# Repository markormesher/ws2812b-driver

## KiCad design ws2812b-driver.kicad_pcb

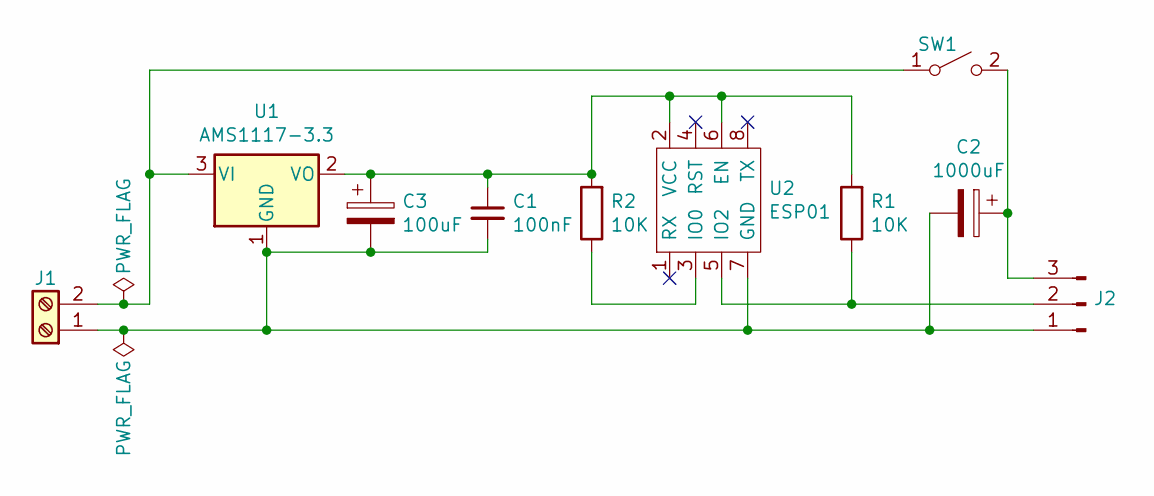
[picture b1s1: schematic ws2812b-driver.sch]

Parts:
C1: 100nF; C_Disc_D5.0mm_W2.5mm_P2.50mm
C2: 1000uF; C_Radial_D10.0mm_H20.0mm_P5.00mm
C3: 100uF; C_Radial_D6.3mm_H11.0mm_P2.50mm
J1: Screw_Terminal_01x02; TerminalBlock_bornier-2_P5.08mm
J2: Conn_01x03_Male; PinHeader_1x03_P2.54mm_Horizontal
R1, R2: 10K; R_Axial_DIN0207_L6.3mm_D2.5mm_P7.62mm_Horizontal
SW1: SW_SPST; PinHeader_1x02_P2.54mm_Vertical
U1: AMS1117-3.3; AMS1117
U2: ESP01; PinSocket_2x04_P2.54mm_Vertical

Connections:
unnamed: C1.1, C3.1, R1.2, R2.2, U1.2 (VO), U2.2 (VCC), U2.6 (EN)
unnamed: C1.2, C2.2, C3.2, J1.1, J2.1, U1.1 (GND), U2.7 (GND)
unnamed: C2.1, J2.3, SW1.2 (B)
unnamed: J1.2, SW1.1 (A), U1.3 (VI)
unnamed: J2.2, R1.1, U2.5 (IO2)
unnamed: R2.1, U2.3 (IO0)

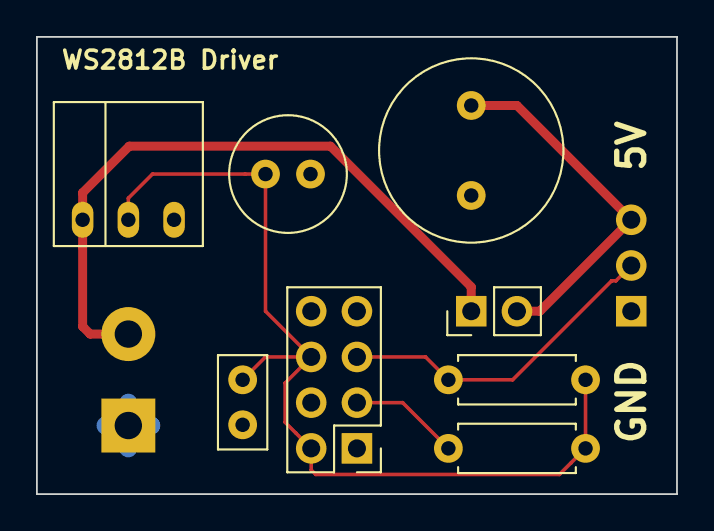
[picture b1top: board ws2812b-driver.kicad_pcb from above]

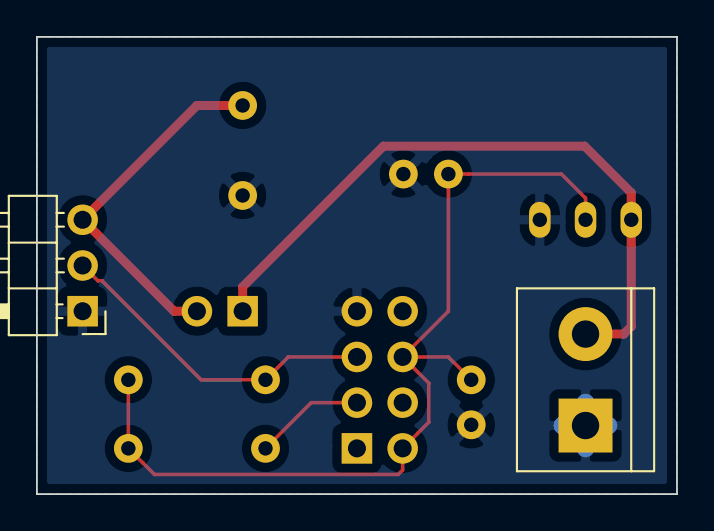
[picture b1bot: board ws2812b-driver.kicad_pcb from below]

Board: 2 copper layers, 35.6 x 25.4 mm, 10 parts (2 on the bottom side), 6 nets.

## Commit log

2020-12-05 initial commit before i lose this pc for a while
